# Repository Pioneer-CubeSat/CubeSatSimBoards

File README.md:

# CubeSatSim Custom PCBs by UW Platteville CubeSat Club

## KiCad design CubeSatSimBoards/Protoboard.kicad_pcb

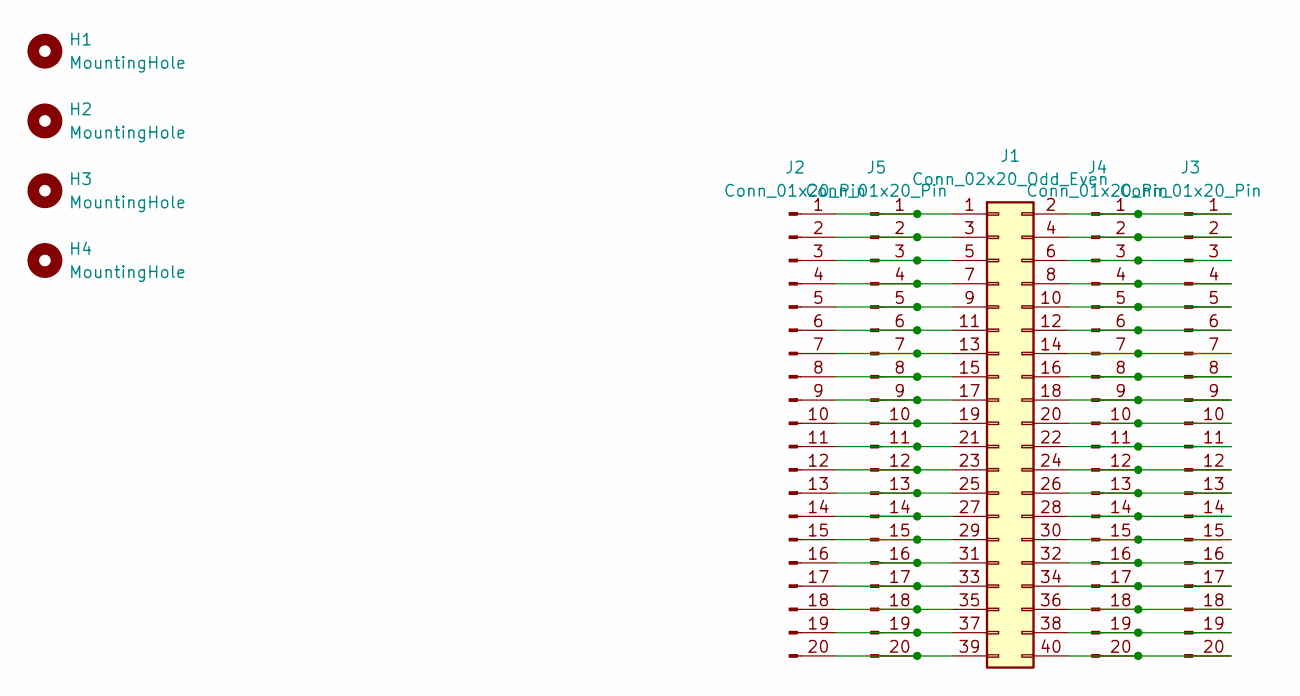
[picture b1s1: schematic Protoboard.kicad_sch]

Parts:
H1, H2, H3, H4: MountingHole; MountingHole_2.7mm_M2.5_ISO14580_Pad
J1: Conn_02x20_Odd_Even; PinHeader_2x20_P2.54mm_Vertical
J2, J3, J4, J5: Conn_01x20_Pin; PinHeader_1x20_P2.54mm_Vertical

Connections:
unnamed: J1.1, J2.1, J5.1
unnamed: J1.2, J3.1, J4.1
unnamed: J1.3, J2.2, J5.2
unnamed: J1.4, J3.2, J4.2
unnamed: J1.5, J2.3, J5.3
unnamed: J1.6, J3.3, J4.3
unnamed: J1.7, J2.4, J5.4
unnamed: J1.8, J3.4, J4.4
unnamed: J1.9, J2.5, J5.5
unnamed: J1.10, J3.5, J4.5
unnamed: J1.11, J2.6, J5.6
unnamed: J1.12, J3.6, J4.6
unnamed: J1.13, J2.7, J5.7
unnamed: J1.14, J3.7, J4.7
unnamed: J1.15, J2.8, J5.8
unnamed: J1.16, J3.8, J4.8
unnamed: J1.17, J2.9, J5.9
unnamed: J1.18, J3.9, J4.9
unnamed: J1.19, J2.10, J5.10
unnamed: J1.20, J3.10, J4.10
unnamed: J1.21, J2.11, J5.11
unnamed: J1.22, J3.11, J4.11
unnamed: J1.23, J2.12, J5.12
unnamed: J1.24, J3.12, J4.12
unnamed: J1.25, J2.13, J5.13
unnamed: J1.26, J3.13, J4.13
unnamed: J1.27, J2.14, J5.14
unnamed: J1.28, J3.14, J4.14
unnamed: J1.29, J2.15, J5.15
unnamed: J1.30, J3.15, J4.15
unnamed: J1.31, J2.16, J5.16
unnamed: J1.32, J3.16, J4.16
unnamed: J1.33, J2.17, J5.17
unnamed: J1.34, J3.17, J4.17
unnamed: J1.35, J2.18, J5.18
unnamed: J1.36, J3.18, J4.18
unnamed: J1.37, J2.19, J5.19
unnamed: J1.38, J3.19, J4.19
unnamed: J1.39, J2.20, J5.20
unnamed: J1.40, J3.20, J4.20

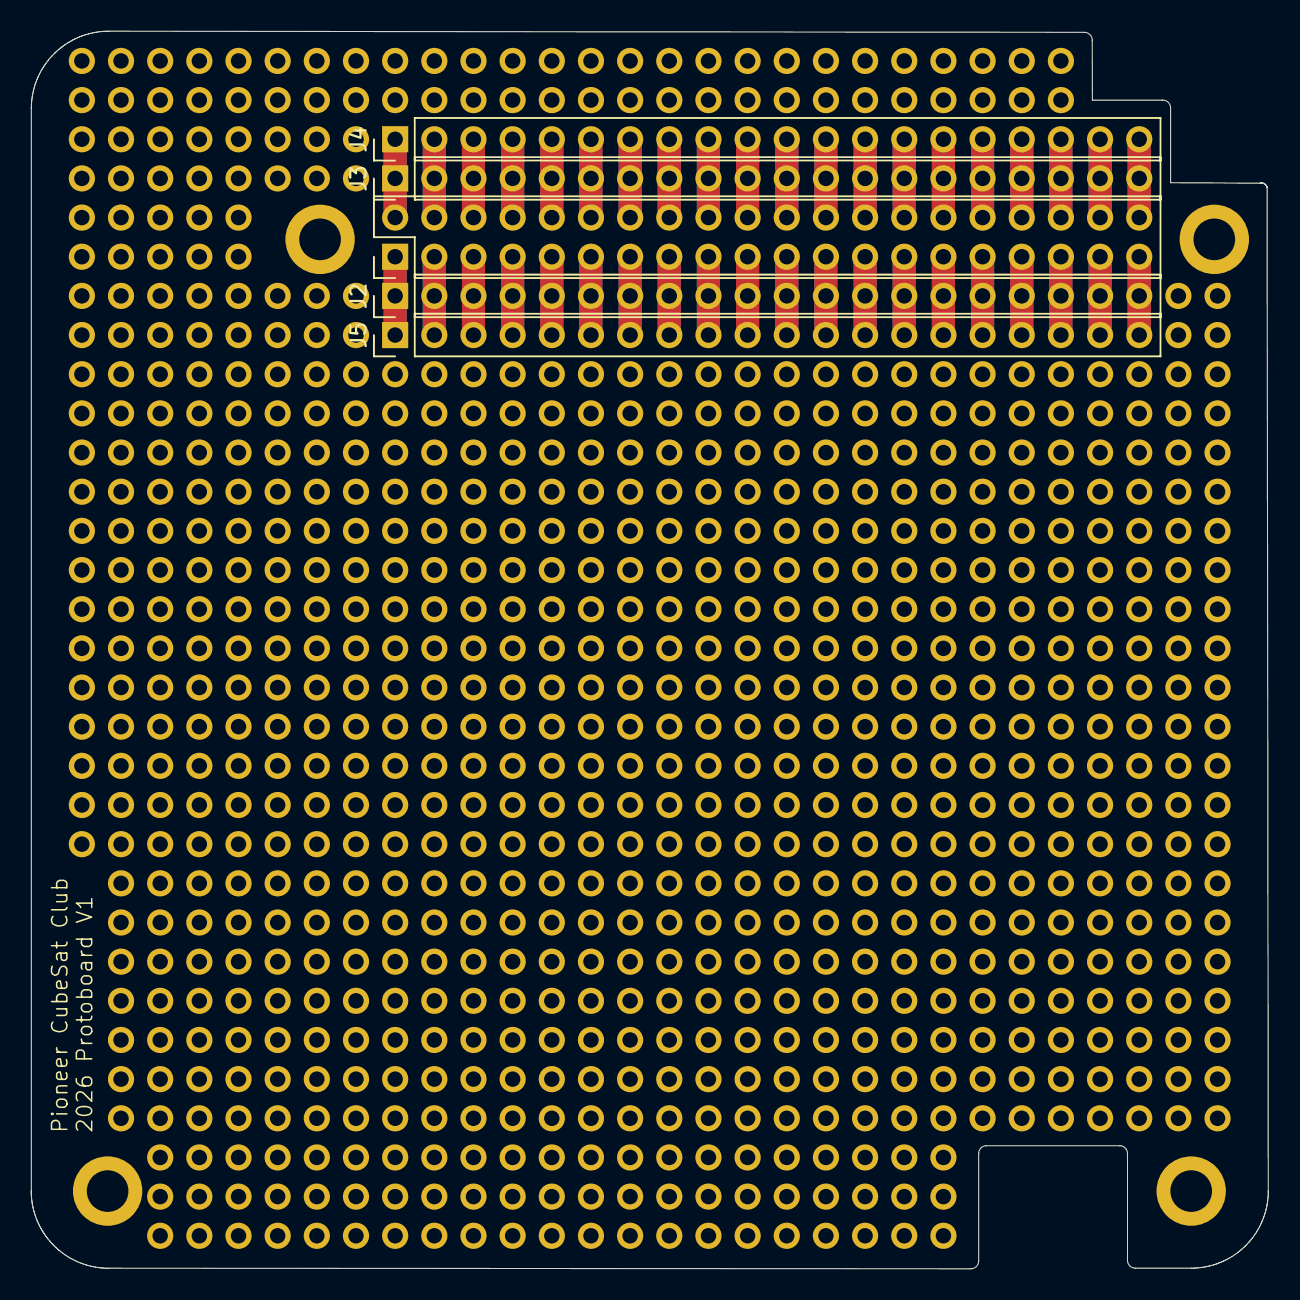
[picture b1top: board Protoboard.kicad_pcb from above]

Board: 2 copper layers, 80.2 x 80.3 mm, 9 parts (0 on the bottom side), 40 nets.
